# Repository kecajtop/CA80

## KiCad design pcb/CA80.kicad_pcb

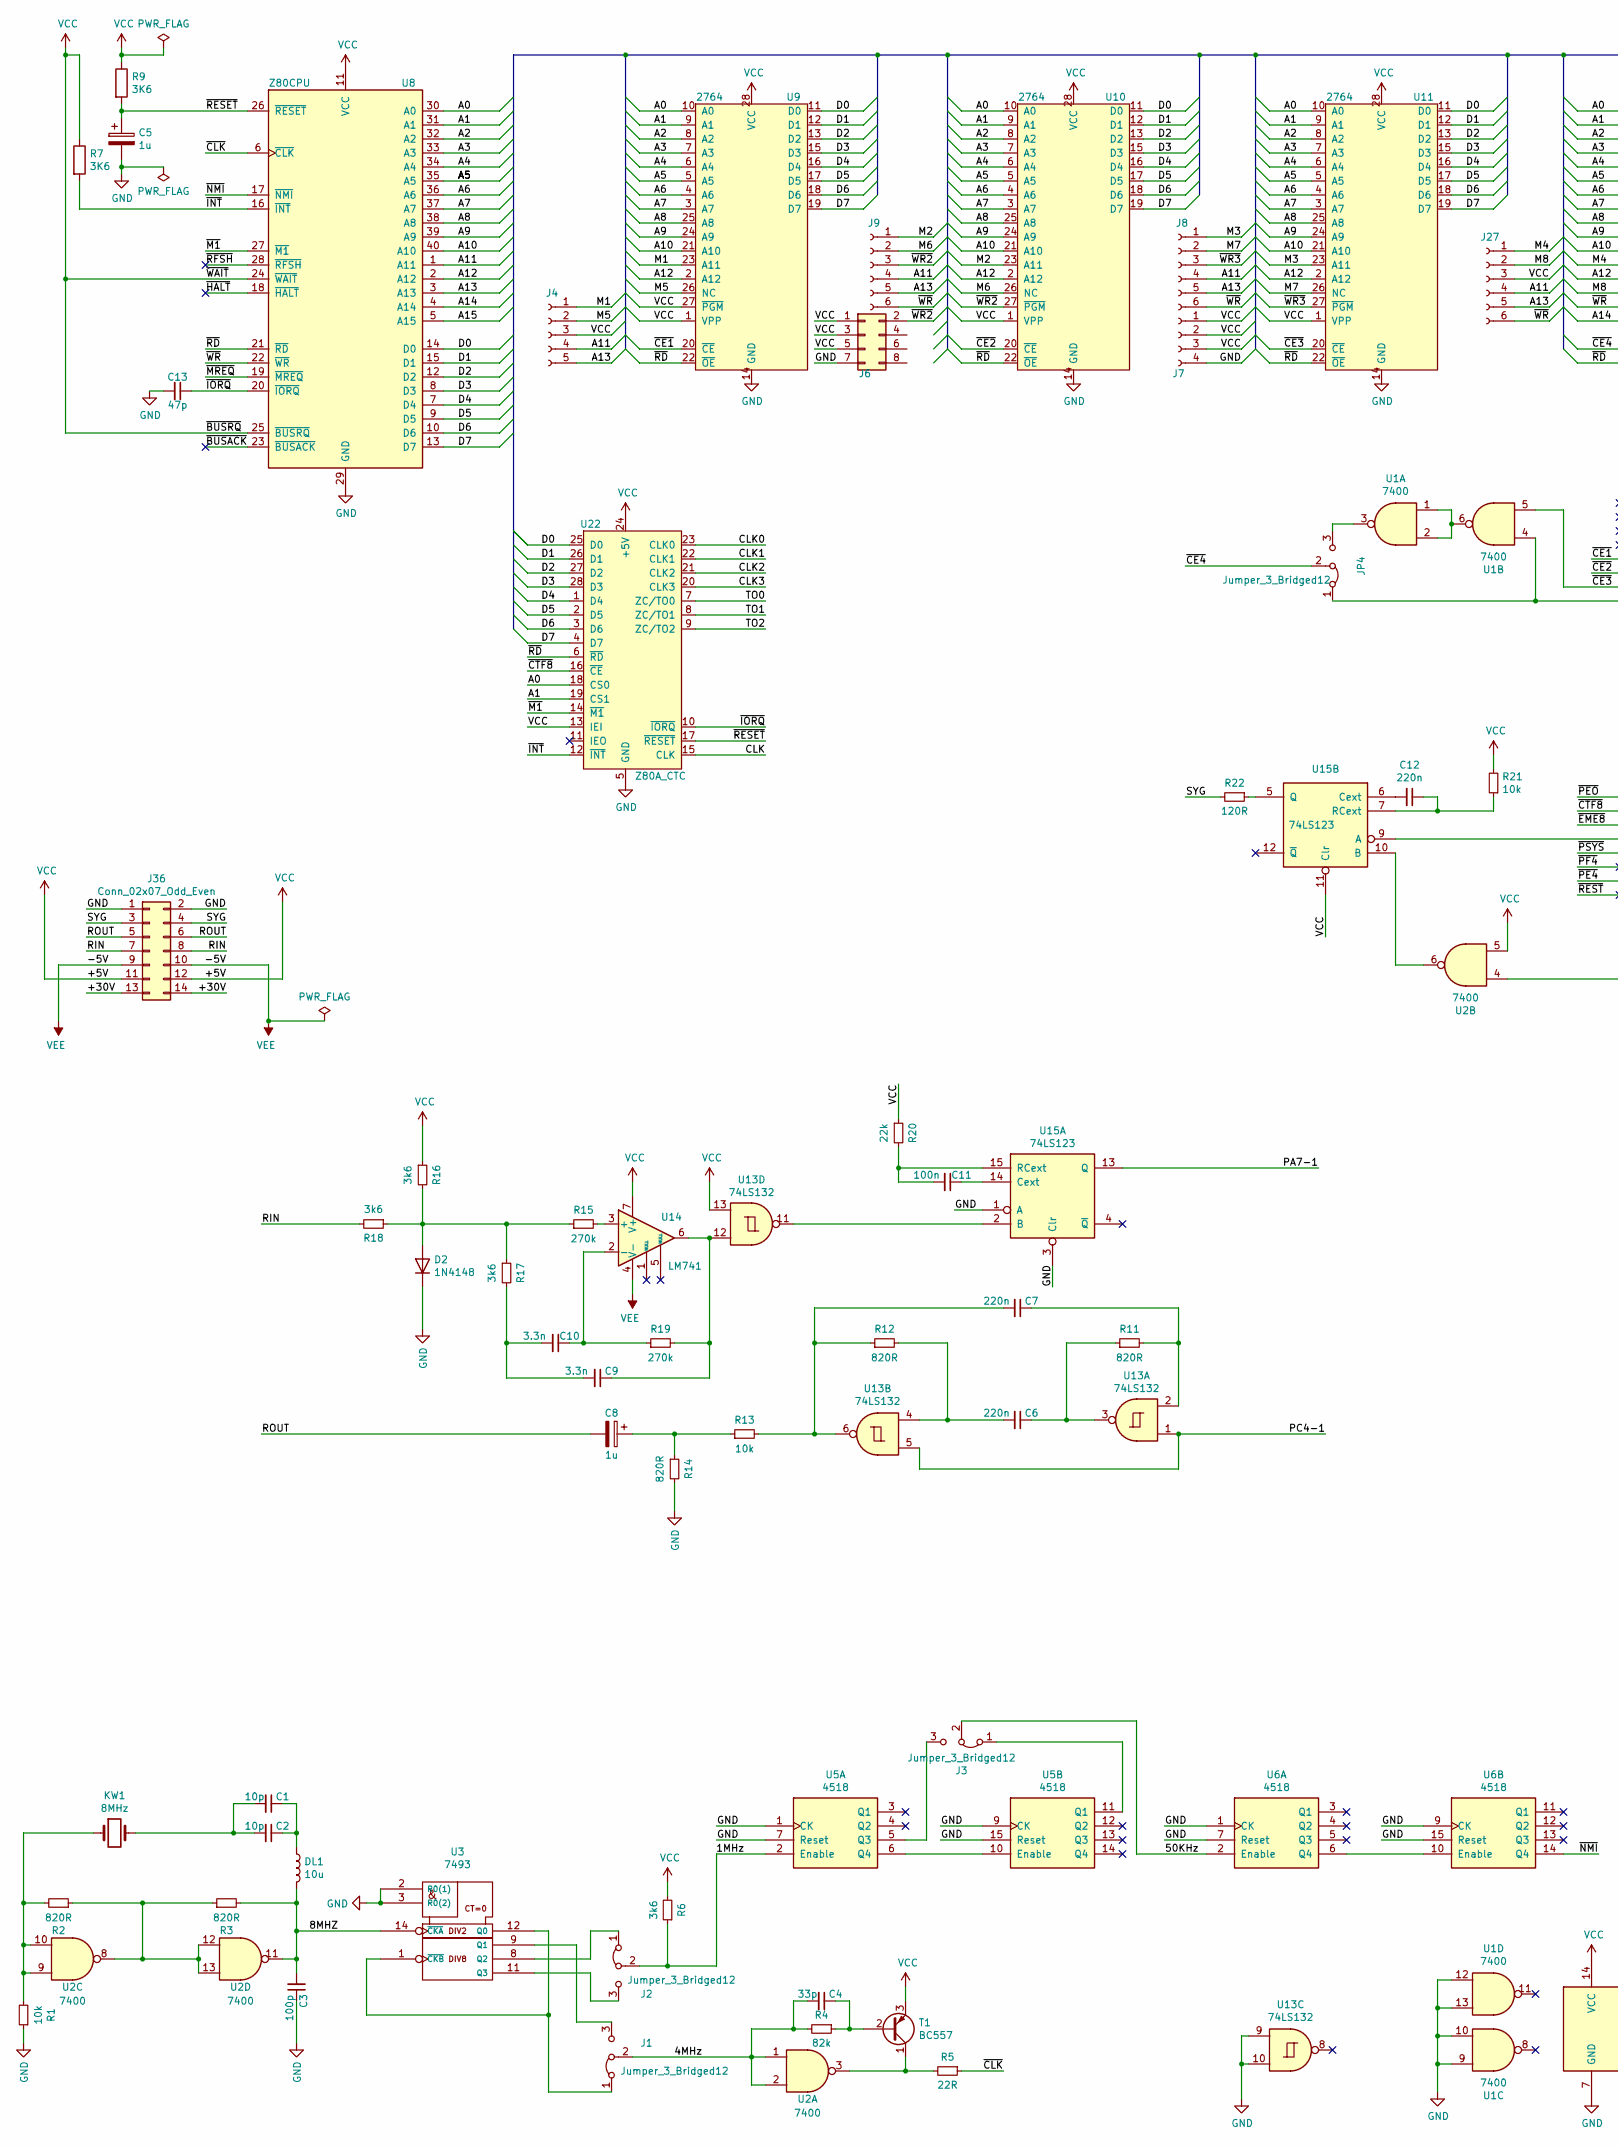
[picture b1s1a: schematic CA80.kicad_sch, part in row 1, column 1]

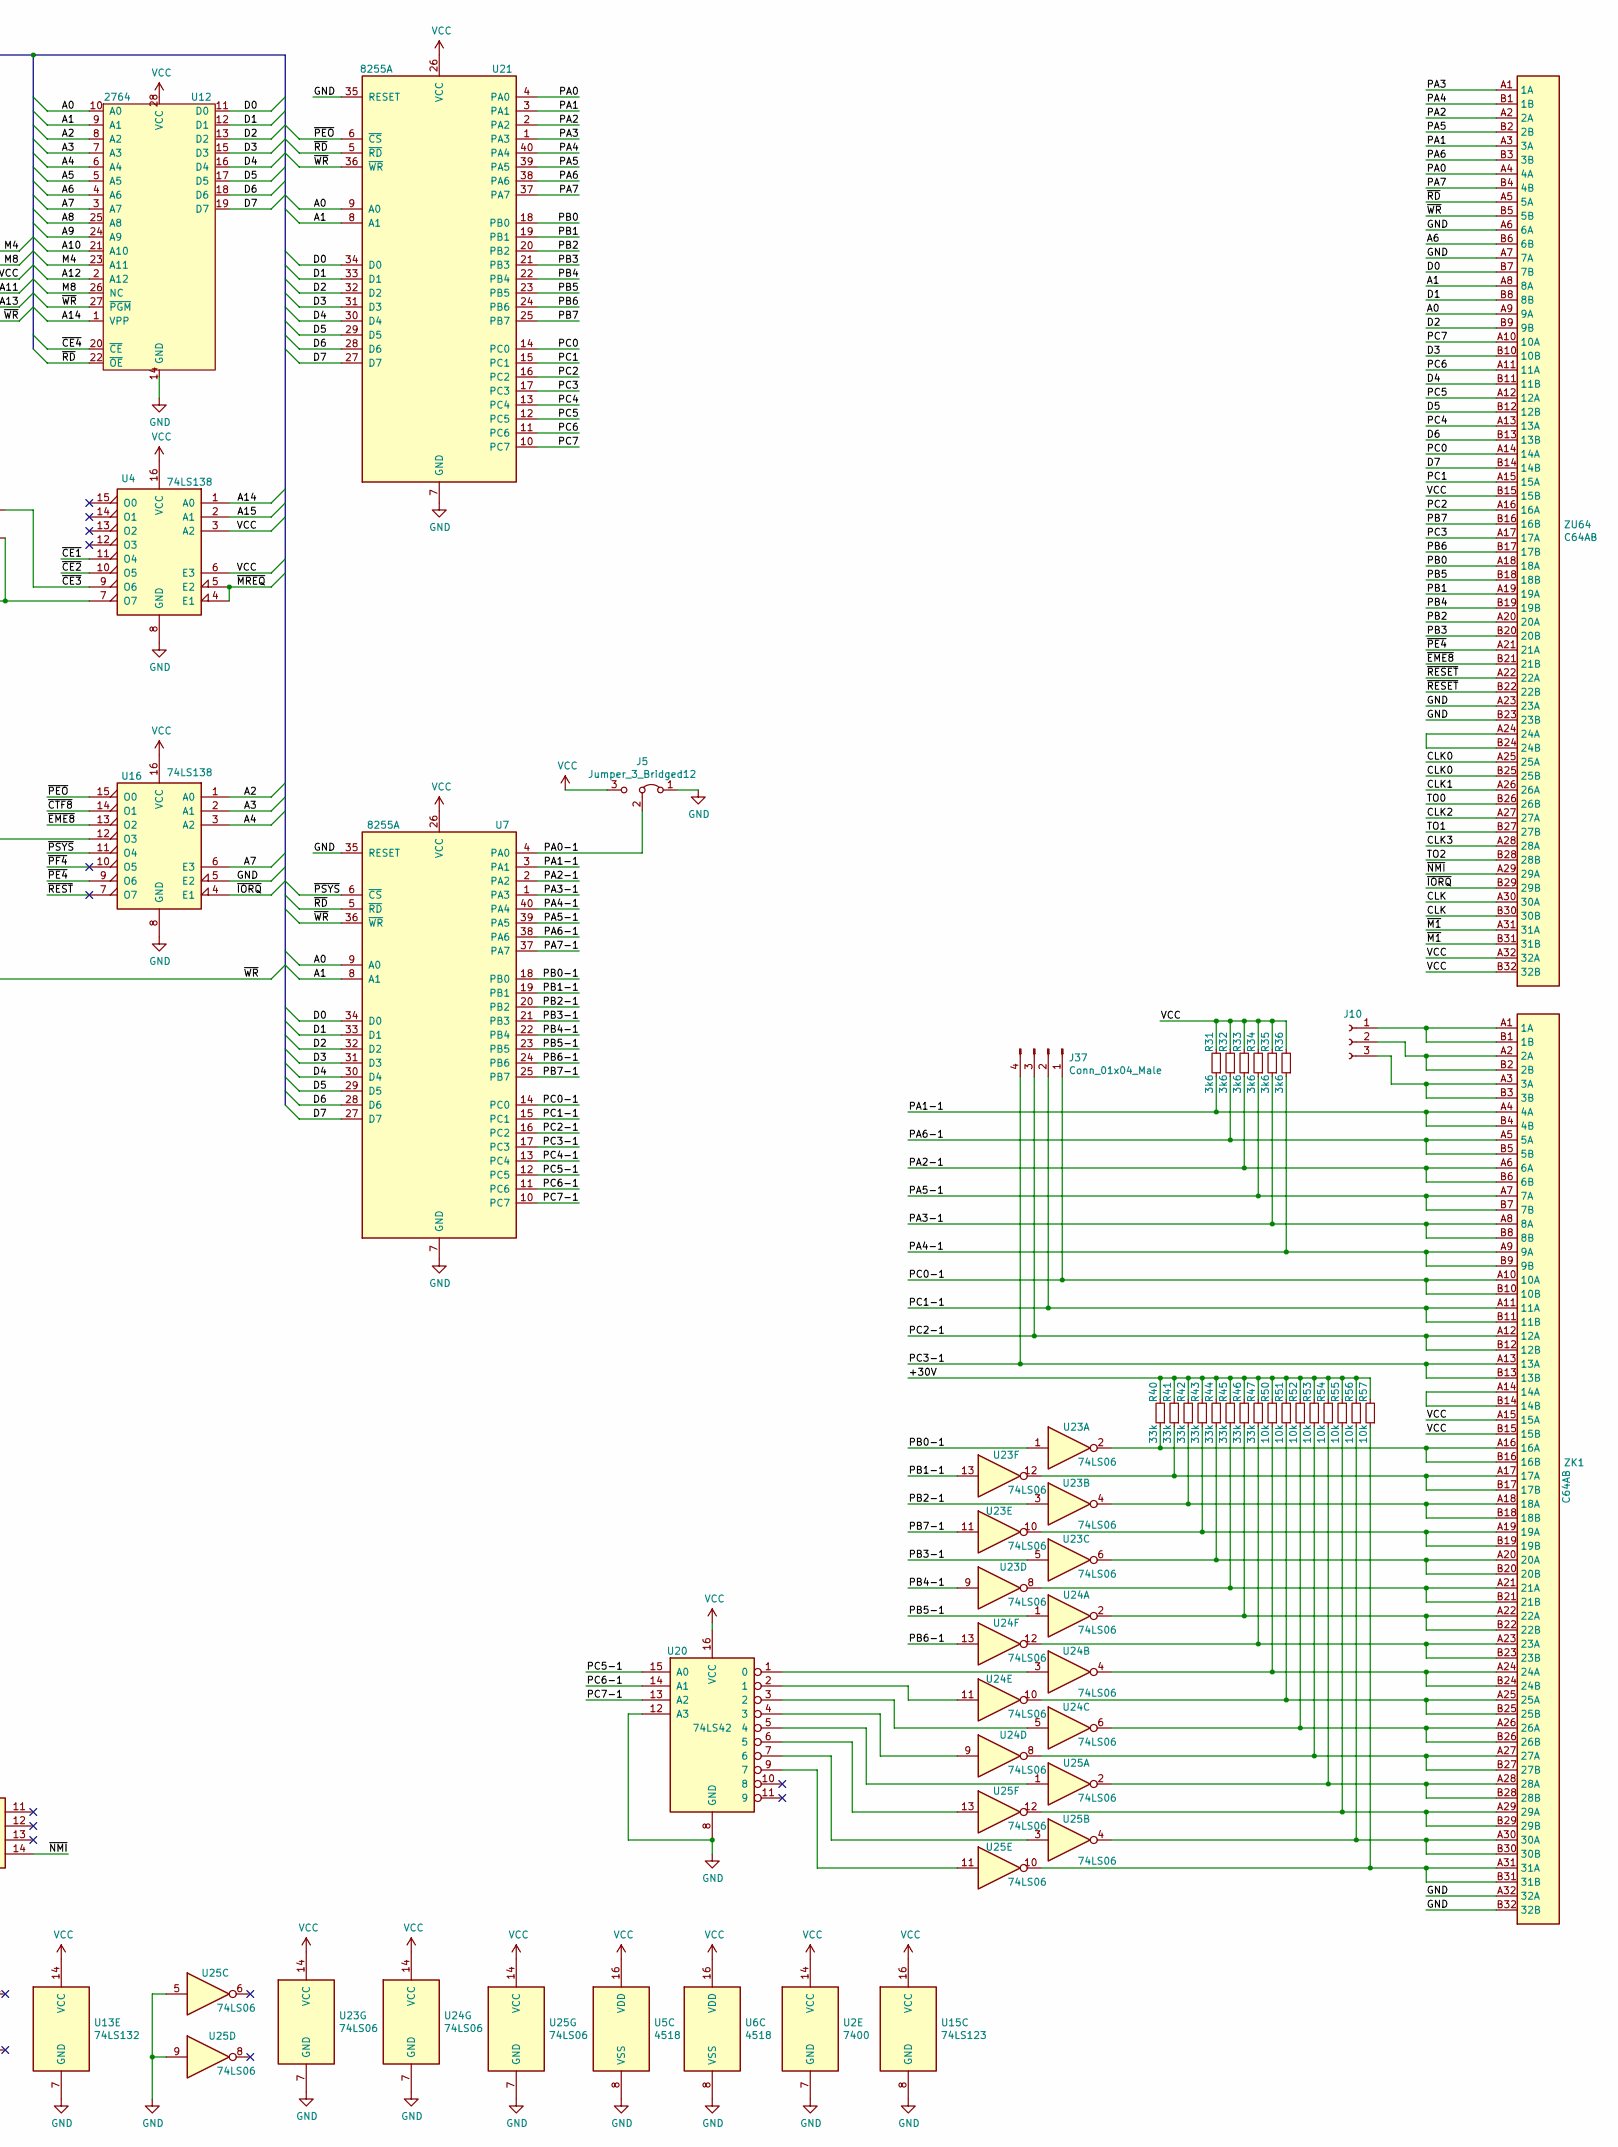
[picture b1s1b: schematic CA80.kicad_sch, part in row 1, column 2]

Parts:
C1, C2: 10p; C_Disc_D7.0mm_W2.5mm_P5.00mm
C3: 100p; C_Disc_D7.0mm_W2.5mm_P5.00mm
C4: 33p; C_Disc_D7.0mm_W2.5mm_P5.00mm
C5, C8: 1u; CP_Radial_D5.0mm_P2.50mm
C6, C7, C12: 220n; C_Disc_D7.0mm_W2.5mm_P5.00mm
C9, C10: 3.3n; C_Disc_D7.0mm_W2.5mm_P5.00mm
C11: 100n; C_Disc_D7.0mm_W2.5mm_P5.00mm
C13: 47p; C_Disc_D7.0mm_W2.5mm_P5.00mm
D2: 1N4148; D_DO-35_SOD27_P7.62mm_Horizontal
DL1: 10u; R_Axial_DIN0207_L6.3mm_D2.5mm_P10.16mm_Horizontal
J1, J2, J3, J5: Jumper_3_Bridged12; PinHeader_1x03_P2.54mm_Vertical
J4: Conn_01x05_Socket; PinHeader_1x05_P2.54mm_Vertical
J6: Conn_02x04_Odd_Even; PinHeader_2x04_P2.54mm_Vertical
J7: Conn_01x04_Socket; PinHeader_1x04_P2.54mm_Vertical
J8, J9, J27: Conn_01x06_Socket; PinHeader_1x06_P2.54mm_Vertical
J10: Conn_01x03_Socket; PinHeader_1x03_P2.54mm_Vertical
J36: Conn_02x07_Odd_Even; PinHeader_2x07_P2.54mm_Horizontal
J37: Conn_01x04_Male
JP4: Jumper_3_Bridged12; PinHeader_1x03_P2.54mm_Vertical
KW1: 8MHz; Crystal_HC49-U_Vertical
R1, R21, R50, R51, R52, R53, R54, R55, R56, R57: 10k; R_Axial_DIN0207_L6.3mm_D2.5mm_P7.62mm_Horizontal
R2, R3: 820R; R_Axial_DIN0207_L6.3mm_D2.5mm_P7.62mm_Horizontal
R4: 82k; R_Axial_DIN0207_L6.3mm_D2.5mm_P7.62mm_Horizontal
R5: 22R; R_Axial_DIN0207_L6.3mm_D2.5mm_P7.62mm_Horizontal
R6, R31, R32, R33, R34, R35, R36: 3k6; R_Axial_DIN0207_L6.3mm_D2.5mm_P7.62mm_Horizontal
R7, R9: 3K6; R_Axial_DIN0207_L6.3mm_D2.5mm_P7.62mm_Horizontal
R11, R12, R14: 820R; R_Axial_DIN0207_L6.3mm_D2.5mm_P10.16mm_Horizontal
R13: 10k; R_Axial_DIN0207_L6.3mm_D2.5mm_P10.16mm_Horizontal
R15, R19: 270k; R_Axial_DIN0207_L6.3mm_D2.5mm_P10.16mm_Horizontal
R16, R17, R18: 3k6; R_Axial_DIN0207_L6.3mm_D2.5mm_P10.16mm_Horizontal
R20: 22k; R_Axial_DIN0207_L6.3mm_D2.5mm_P10.16mm_Horizontal
R22: 120R; R_Axial_DIN0207_L6.3mm_D2.5mm_P7.62mm_Horizontal
R40, R41, R42, R43, R44, R45, R46, R47: 33k; R_Axial_DIN0207_L6.3mm_D2.5mm_P7.62mm_Horizontal
T1: BC557; TO-92_Inline
U1, U2: 7400; DIP-14_W7.62mm
U3: 7493; DIP-14_W7.62mm_Socket
U4, U16: 74LS138; DIP-16_W7.62mm
U5, U6: 4518; DIP-16_W7.62mm
U7, U21: 8255A; DIP-40_W15.24mm
U8: Z80CPU; DIP-40_W15.24mm
U9, U10, U11, U12: 2764; DIP-28_W15.24mm
U13: 74LS132; DIP-14_W7.62mm
U14: LM741; DIP-8_W7.62mm
U15: 74LS123; DIP-16_W7.62mm
U20: 74LS42; DIP-16_W7.62mm
U22: Z80A_CTC; DIP-28_W15.24mm
U23, U24, U25: 74LS06; DIP-14_W7.62mm
ZK1: C64AB; DIN41612_B_2x32_Horizontal
ZU64: C64AB; DIN41612_B_2x32_Vertical

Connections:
/1MHz: J2.2 (C), R6.1, U5.2 (Enable)
/4MHz: C4.2, J1.2 (C), R4.2, U2.1, U2.2
/8MHZ: C3.2, DL1.2, R3.2, U2.11, U3.14 (~CKA)
/50KHz: J3.2 (C), U6.2 (Enable)
/+30V: J36.13, J36.14, R40.2, R41.2, R42.2, R43.2, R44.2, R45.2, R46.2, R47.2, R50.2, R51.2, R52.2, R53.2, R54.2, R55.2, R56.2, R57.2
/A0: U7.9 (A0), U8.30 (A0), U9.10 (A0), U10.10 (A0), U11.10 (A0), U12.10 (A0), U21.9 (A0), U22.18 (CS0), ZU64.A9 (9A)
/A1: U7.8 (A1), U8.31 (A1), U9.9 (A1), U10.9 (A1), U11.9 (A1), U12.9 (A1), U21.8 (A1), U22.19 (CS1), ZU64.A8 (8A)
/A2: U8.32 (A2), U9.8 (A2), U10.8 (A2), U11.8 (A2), U12.8 (A2), U16.1 (A0)
/A3: U8.33 (A3), U9.7 (A3), U10.7 (A3), U11.7 (A3), U12.7 (A3), U16.2 (A1)
/A4: U8.34 (A4), U9.6 (A4), U10.6 (A4), U11.6 (A4), U12.6 (A4), U16.3 (A2)
/A5: U8.35 (A5), U9.5 (A5), U10.5 (A5), U11.5 (A5), U12.5 (A5)
/A6: U8.36 (A6), U9.4 (A6), U10.4 (A6), U11.4 (A6), U12.4 (A6), ZU64.B6 (6B)
/A7: U8.37 (A7), U9.3 (A7), U10.3 (A7), U11.3 (A7), U12.3 (A7), U16.6 (E3)
/A8: U8.38 (A8), U9.25 (A8), U10.25 (A8), U11.25 (A8), U12.25 (A8)
/A9: U8.39 (A9), U9.24 (A9), U10.24 (A9), U11.24 (A9), U12.24 (A9)
/A10: U8.40 (A10), U9.21 (A10), U10.21 (A10), U11.21 (A10), U12.21 (A10)
/A11: J4.4, J8.4, J9.4, J27.4, U8.1 (A11)
/A12: U8.2 (A12), U9.2 (A12), U10.2 (A12), U11.2 (A12), U12.2 (A12)
/A13: J4.5, J8.5, J9.5, J27.5, U8.3 (A13)
/A14: U4.1 (A0), U8.4 (A14), U12.1 (VPP)
/A15: U4.2 (A1), U8.5 (A15)
/CLK: U22.15 (CLK), ZU64.A30 (30A), ZU64.B30 (30B)
/CLK0: U22.23 (CLK0), ZU64.A25 (25A), ZU64.B25 (25B)
/CLK1: U22.22 (CLK1), ZU64.A26 (26A)
/CLK2: U22.21 (CLK2), ZU64.A27 (27A)
/CLK3: U22.20 (CLK3), ZU64.A28 (28A)
/D0: U7.34 (D0), U8.14 (D0), U9.11 (D0), U10.11 (D0), U11.11 (D0), U12.11 (D0), U21.34 (D0), U22.25 (D0), ZU64.B7 (7B)
/D1: U7.33 (D1), U8.15 (D1), U9.12 (D1), U10.12 (D1), U11.12 (D1), U12.12 (D1), U21.33 (D1), U22.26 (D1), ZU64.B8 (8B)
/D2: U7.32 (D2), U8.12 (D2), U9.13 (D2), U10.13 (D2), U11.13 (D2), U12.13 (D2), U21.32 (D2), U22.27 (D2), ZU64.B9 (9B)
/D3: U7.31 (D3), U8.8 (D3), U9.15 (D3), U10.15 (D3), U11.15 (D3), U12.15 (D3), U21.31 (D3), U22.28 (D3), ZU64.B10 (10B)
/D4: U7.30 (D4), U8.7 (D4), U9.16 (D4), U10.16 (D4), U11.16 (D4), U12.16 (D4), U21.30 (D4), U22.1 (D4), ZU64.B11 (11B)
/D5: U7.29 (D5), U8.9 (D5), U9.17 (D5), U10.17 (D5), U11.17 (D5), U12.17 (D5), U21.29 (D5), U22.2 (D5), ZU64.B12 (12B)
/D6: U7.28 (D6), U8.10 (D6), U9.18 (D6), U10.18 (D6), U11.18 (D6), U12.18 (D6), U21.28 (D6), U22.3 (D6), ZU64.B13 (13B)
/D7: U7.27 (D7), U8.13 (D7), U9.19 (D7), U10.19 (D7), U11.19 (D7), U12.19 (D7), U21.27 (D7), U22.4 (D7), ZU64.B14 (14B)
/M1: J4.1, U9.23 (A11)
/M2: J9.1, U10.23 (A11)
/M3: J8.1, U11.23 (A11)
/M4: J27.1, U12.23 (A11)
/M5: J4.2, U9.26 (NC)
/M6: J9.2, U10.26 (NC)
/M7: J8.2, U11.26 (NC)
/M8: J27.2, U12.26 (NC)
/PA0: U21.4 (PA0), ZU64.A4 (4A)
/PA0-1: J5.2 (C), U7.4 (PA0)
/PA1: U21.3 (PA1), ZU64.A3 (3A)
/PA1-1: R31.1, U7.3 (PA1), ZK1.A4 (4A), ZK1.B4 (4B)
/PA2: U21.2 (PA2), ZU64.A2 (2A)
/PA2-1: R33.1, U7.2 (PA2), ZK1.A6 (6A), ZK1.B6 (6B)
/PA3: U21.1 (PA3), ZU64.A1 (1A)
/PA3-1: R35.1, U7.1 (PA3), ZK1.A8 (8A), ZK1.B8 (8B)
/PA4: U21.40 (PA4), ZU64.B1 (1B)
/PA4-1: R36.1, U7.40 (PA4), ZK1.A9 (9A), ZK1.B9 (9B)
/PA5: U21.39 (PA5), ZU64.B2 (2B)
/PA5-1: R34.1, U7.39 (PA5), ZK1.A7 (7A), ZK1.B7 (7B)
/PA6: U21.38 (PA6), ZU64.B3 (3B)
/PA6-1: R32.1, U7.38 (PA6), ZK1.A5 (5A), ZK1.B5 (5B)
/PA7: U21.37 (PA7), ZU64.B4 (4B)
/PA7-1: U7.37 (PA7), U15.13 (Q)
/PB0: U21.18 (PB0), ZU64.A18 (18A)
/PB0-1: U7.18 (PB0), U23.1
/PB1: U21.19 (PB1), ZU64.A19 (19A)
/PB1-1: U7.19 (PB1), U23.13
/PB2: U21.20 (PB2), ZU64.A20 (20A)
/PB2-1: U7.20 (PB2), U23.3
/PB3: U21.21 (PB3), ZU64.B20 (20B)
/PB3-1: U7.21 (PB3), U23.5
/PB4: U21.22 (PB4), ZU64.B19 (19B)
/PB4-1: U7.22 (PB4), U23.9
/PB5: U21.23 (PB5), ZU64.B18 (18B)
/PB5-1: U7.23 (PB5), U24.1
/PB6: U21.24 (PB6), ZU64.B17 (17B)
/PB6-1: U7.24 (PB6), U24.13
/PB7: U21.25 (PB7), ZU64.B16 (16B)
/PB7-1: U7.25 (PB7), U23.11
/PC0: U21.14 (PC0), ZU64.A14 (14A)
/PC0-1: J37.1, U7.14 (PC0), ZK1.A10 (10A), ZK1.B10 (10B)
/PC1: U21.15 (PC1), ZU64.A15 (15A)
/PC1-1: J37.2, U7.15 (PC1), ZK1.A11 (11A), ZK1.B11 (11B)
/PC2: U21.16 (PC2), ZU64.A16 (16A)
/PC2-1: J37.3, U7.16 (PC2), ZK1.A12 (12A), ZK1.B12 (12B)
/PC3: U21.17 (PC3), ZU64.A17 (17A)
/PC3-1: J37.4, U7.17 (PC3), ZK1.A13 (13A), ZK1.B13 (13B)
/PC4: U21.13 (PC4), ZU64.A13 (13A)
/PC4-1: U7.13 (PC4), U13.1, U13.5
/PC5: U21.12 (PC5), ZU64.A12 (12A)
/PC5-1: U7.12 (PC5), U20.15 (A0)
/PC6: U21.11 (PC6), ZU64.A11 (11A)
/PC6-1: U7.11 (PC6), U20.14 (A1)
/PC7: U21.10 (PC7), ZU64.A10 (10A)
/PC7-1: U7.10 (PC7), U20.13 (A2)
/RIN: J36.7, J36.8, R18.2
/ROUT: C8.2, J36.5, J36.6
/SYG: J36.3, J36.4, R22.2
/TO0: U22.7 (ZC/TO0), ZU64.B26 (26B)
/TO1: U22.8 (ZC/TO1), ZU64.B27 (27B)
/TO2: U22.9 (ZC/TO2), ZU64.B28 (28B)
/~BUSACK: U8.23 (~BUSACK)
/~CE1: U4.11 (O4), U9.20 (~CE)
/~CE2: U4.10 (O5), U10.20 (~CE)
/~CE3: U1.5, U4.9 (O6), U11.20 (~CE)
/~CE4: JP4.2 (C), U12.20 (~CE)
/~CLK: R5.1, U8.6 (~CLK)
/~CTF8: U16.14 (O1), U22.16 (~CE)
/~EME8: U16.13 (O2), ZU64.B21 (21B)
/~HALT: U8.18 (~HALT)
/~INT: R7.2, U8.16 (~INT), U22.12 (~INT)
/~IORQ: C13.1, U8.20 (~IORQ), U16.4 (E1), U22.10 (~IORQ), ZU64.B29 (29B)
/~M1: U8.27 (~M1), U22.14 (~M1), ZU64.A31 (31A), ZU64.B31 (31B)
/~MREQ: U4.4 (E1), U4.5 (E2), U8.19 (~MREQ)
/~NMI: U6.14 (Q4), U8.17 (~NMI), ZU64.A29 (29A)
/~PE4: U16.9 (O6), ZU64.A21 (21A)
/~PEO: U16.15 (O0), U21.6 (~CS)
/~PF4: U16.10 (O5)
/~PSYS: U7.6 (~CS), U16.11 (O4)
/~RD: U7.5 (~RD), U8.21 (~RD), U9.22 (~OE), U10.22 (~OE), U11.22 (~OE), U12.22 (~OE), U21.5 (~RD), U22.6 (~RD), ZU64.A5 (5A)
/~RESET: C5.1, R9.2, U8.26 (~RESET), U22.17 (~RESET), ZU64.A22 (22A), ZU64.B22 (22B)
/~REST: U16.7 (O7)
/~RFSH: U8.28 (~RFSH)
/~WR2: J6.2, J9.3, U10.27 (~PGM)
/~WR3: J8.3, U11.27 (~PGM)
/~WR: J8.6, J9.6, J27.6, U2.4, U7.36 (~WR), U8.22 (~WR), U12.27 (~PGM), U21.36 (~WR), ZU64.B5 (5B)
GND: C3.1, C5.2, C13.2, D2.1 (K), J5.1 (A), J6.7, J7.4, J36.1, J36.2, R1.1, R14.2, U1.9, U1.10, U1.12, U1.13, U2.7 (GND), U3.2 (R0(1)), U3.3 (R0(2)), U4.8 (GND), U5.1 (CK), U5.7 (Reset), U5.8 (VSS), U5.9 (CK), U5.15 (Reset), U6.1 (CK), U6.7 (Reset), U6.8 (VSS), U6.9 (CK), U6.15 (Reset), U7.7 (GND), U7.35 (RESET), U8.29 (GND), U9.14 (GND), U10.14 (GND), U11.14 (GND), U12.14 (GND), U13.7 (GND), U13.9, U13.10, U15.1 (A), U15.3 (Clr), U15.8 (GND), U16.5 (E2), U16.8 (GND), U20.8 (GND), U20.12 (A3), U21.7 (GND), U21.35 (RESET), U22.5 (GND), U23.7 (GND), U24.7 (GND), U25.5, U25.7 (GND), U25.9, ZK1.A32 (32A), ZK1.B32 (32B), ZU64.A6 (6A), ZU64.A7 (7A), ZU64.A23 (23A), ZU64.B23 (23B)
unnamed: C1.1, C2.1, DL1.1
unnamed: C1.2, C2.2, KW1.2
unnamed: C6.1, R11.1, U13.3
unnamed: C6.2, R12.2, U13.4
unnamed: C7.1, R11.2, U13.2
unnamed: C7.2, R12.1, R13.2, U13.6
unnamed: C8.1, R13.1, R14.1
unnamed: C9.1, R19.2, U13.12, U14.6
unnamed: C9.2, C10.2, R17.2
unnamed: D2.2 (A), R15.1, R16.2, R17.1, R18.1
unnamed: J1.1 (A), U3.1 (~CKB), U3.12 (Q0)
unnamed: J1.3 (B), U3.9 (Q1)
unnamed: J2.1 (A), U3.8 (Q2)
unnamed: J2.3 (B), U3.11 (Q3)
unnamed: J3.1 (A), U5.11 (Q1)
unnamed: J3.3 (B), U5.5 (Q3)
unnamed: J10.1, ZK1.A1 (1A), ZK1.B1 (1B)
unnamed: J10.2, ZK1.A2 (2A), ZK1.B2 (2B)
unnamed: J10.3, ZK1.A3 (3A), ZK1.B3 (3B)
unnamed: JP4.1 (A), U1.4, U4.7 (O7)
unnamed: JP4.3 (B), U1.3
unnamed: KW1.1, R1.2, R2.2, U2.9, U2.10
unnamed: R2.1, R3.1, U2.8, U2.12, U2.13
unnamed: C4.1, R4.1, T1.2 (B)
unnamed: R5.2, T1.1 (C), U2.3
unnamed: U1.1, U1.2, U1.6
unnamed: U5.6 (Q4), U5.10 (Enable)
unnamed: U6.6 (Q4), U6.10 (Enable)
unnamed: R15.2, U14.3 (+)
unnamed: C10.1, R19.1, U14.2 (-)
unnamed: U13.11, U15.2 (B)
unnamed: C11.1, U15.14 (Cext)
unnamed: C11.2, R20.2, U15.15 (RCext)
unnamed: U15.9 (A), U16.12 (O3)
unnamed: U2.6, U15.10 (B)
unnamed: C12.2, U15.6 (Cext)
unnamed: R22.1, U15.5 (Q)
unnamed: C12.1, R21.1, U15.7 (RCext)
unnamed: U20.1 (0), U24.3
unnamed: U20.2 (1), U24.11
unnamed: U20.3 (2), U24.5
unnamed: U20.4 (3), U24.9
unnamed: U20.5 (4), U25.1
unnamed: U20.6 (5), U25.13
unnamed: U20.7 (6), U25.3
unnamed: U20.9 (7), U25.11
unnamed: ZK1.A14 (14A), ZK1.B14 (14B)
unnamed: R40.1, U23.2, ZK1.A16 (16A), ZK1.B16 (16B)
unnamed: R41.1, U23.12, ZK1.A17 (17A), ZK1.B17 (17B)
unnamed: R42.1, U23.4, ZK1.A18 (18A), ZK1.B18 (18B)
unnamed: R43.1, U23.10, ZK1.A19 (19A), ZK1.B19 (19B)
unnamed: R44.1, U23.6, ZK1.A20 (20A), ZK1.B20 (20B)
unnamed: R45.1, U23.8, ZK1.A21 (21A), ZK1.B21 (21B)
unnamed: R46.1, U24.2, ZK1.A22 (22A), ZK1.B22 (22B)
unnamed: R47.1, U24.12, ZK1.A23 (23A), ZK1.B23 (23B)
unnamed: R50.1, U24.4, ZK1.A24 (24A), ZK1.B24 (24B)
unnamed: R51.1, U24.10, ZK1.A25 (25A), ZK1.B25 (25B)
unnamed: R52.1, U24.6, ZK1.A26 (26A), ZK1.B26 (26B)
unnamed: R53.1, U24.8, ZK1.A27 (27A), ZK1.B27 (27B)
unnamed: R54.1, U25.2, ZK1.A28 (28A), ZK1.B28 (28B)
unnamed: R55.1, U25.12, ZK1.A29 (29A), ZK1.B29 (29B)
unnamed: R56.1, U25.4, ZK1.A30 (30A), ZK1.B30 (30B)
unnamed: R57.1, U25.10, ZK1.A31 (31A), ZK1.B31 (31B)
unnamed: ZU64.A24 (24A), ZU64.B24 (24B)
VCC: J4.3, J5.3 (B), J6.1, J6.3, J6.5, J7.1, J7.2, J7.3, J27.3, J36.11, J36.12, R6.2, R7.1, R9.1, R16.1, R20.1, R21.2, R31.2, R32.2, R33.2, R34.2, R35.2, R36.2, T1.3 (E), U2.5, U2.14 (VCC), U3.5 (VCC), U4.3 (A2), U4.6 (E3), U4.16 (VCC), U5.16 (VDD), U6.16 (VDD), U7.26 (VCC), U8.11 (VCC), U8.24 (~WAIT), U8.25 (~BUSRQ), U9.1 (VPP), U9.27 (~PGM), U9.28 (VCC), U10.1 (VPP), U10.28 (VCC), U11.1 (VPP), U11.28 (VCC), U12.28 (VCC), U13.13, U13.14 (VCC), U14.7 (V+), U15.11 (Clr), U15.16 (VCC), U16.16 (VCC), U20.16 (VCC), U21.26 (VCC), U22.13 (IEI), U22.24 (+5V), U23.14 (VCC), U24.14 (VCC), U25.14 (VCC), ZK1.A15 (15A), ZK1.B15 (15B), ZU64.A32 (32A), ZU64.B15 (15B), ZU64.B32 (32B)
VEE: J36.9, J36.10, U14.4 (V-)

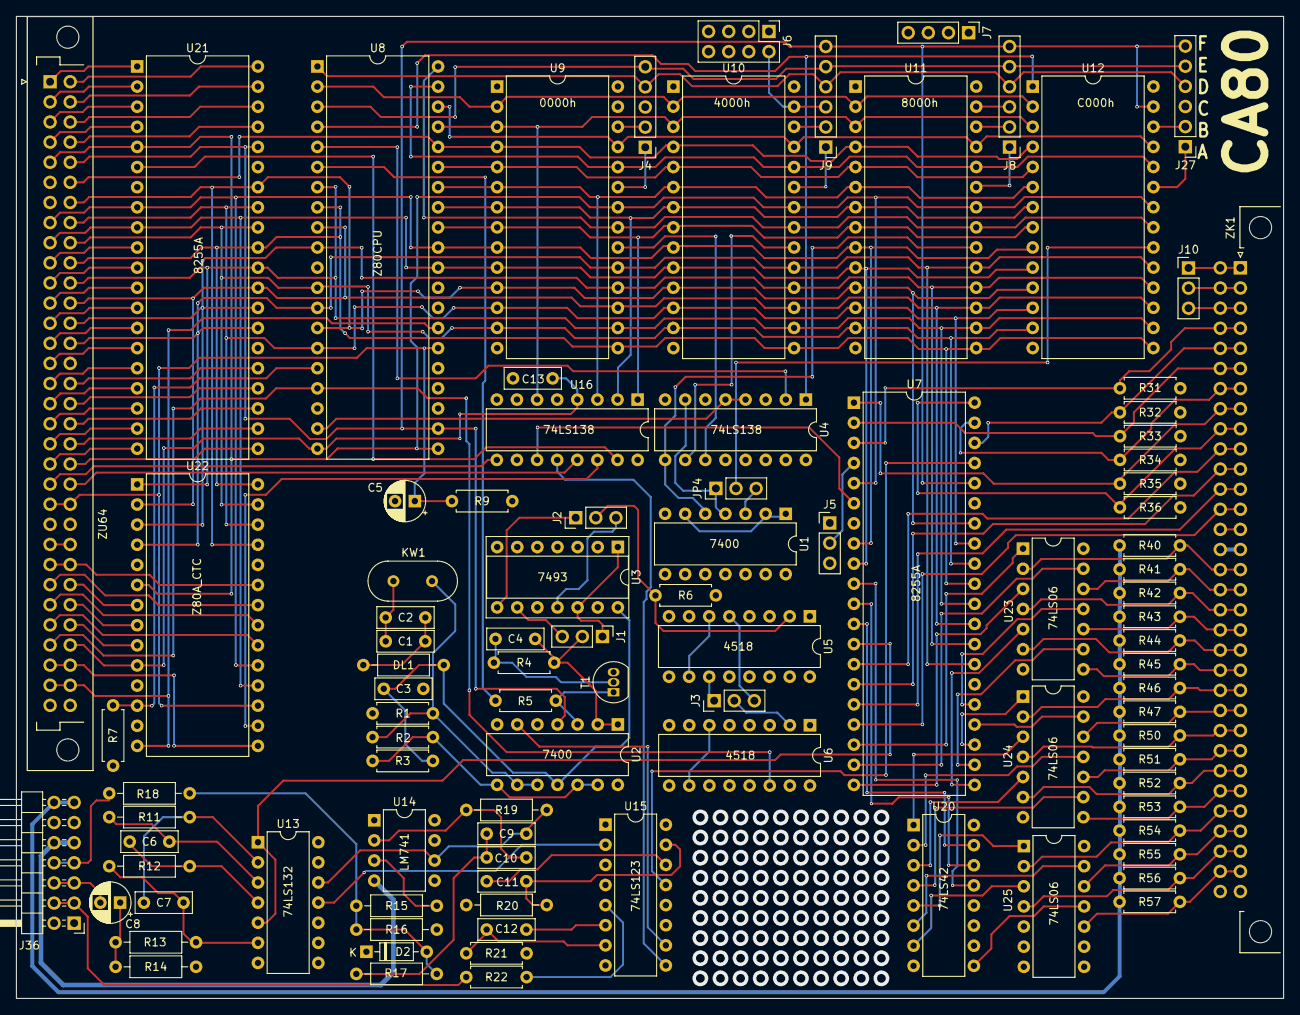
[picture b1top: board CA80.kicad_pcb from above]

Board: 4 copper layers, 160.0 x 124.0 mm, 96 parts (0 on the bottom side), 183 nets.

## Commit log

2023-10-18 First content upload
